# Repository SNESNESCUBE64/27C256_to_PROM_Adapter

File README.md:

# 27C256 to PROM Adapter

The purpose of this repo is to replace the old obselete PROMs. It is recommended that you use the Atmel AT27C256-45PU. It is a very fast OTP EPROM that can be purchased from reputable sellers such as mouser.com. All board designs are done in Kicad.

*Just as a disclaimer, these are not garunteed to work with everything. Not all of the adapters have been verified to work. As these are verified working, the table will be updated.*

## Chip Verification
| Chip   | Boards Made? | Verified Working? | Test Details                                                                      |
|--------|--------------|-------------------|-----------------------------------------------------------------------------------|
| 82S123 | No           | No                | Untested                                                                          |
| 82S126 | Yes          | No                | Untested                                                                          |
| 82S129 | Yes          | Yes               | Tested audio PROM 1D and Color PROM 1C on Galaga, ran for 4 hours with no issues  |
| 82S130 | Yes          | No                | Untested                                                                          |
| 82S131 | Yes          | No                | Untested                                                                          |
| 82S135 | No           | No                | Untested                                                                          |
| 82S137 | No           | No                | Untested                                                                          |
| 82S141 | No           | No                | Untested                                                                          |
| 82S141 | No           | No                | Untested                                                                          |
| 82S147 | No           | No                | Untested                                                                          |
|TKG Elim| Yes          | Yes               | Tested working on a TRS2 Radarscope PCB set. Ran with no issues.                  |

## 82S123
Just a drop in replacement, no jumpers or anything. Just solder the pins, burn the rom, then solder the rom and insert in the socket!

## 82S126/82S129/82S130/82S131
There are two jumpers, for 82S130/82S131, jump pins 1 and 2 for both jumper sets. For 82S126/82S129, jump pins 2 and 3 for both jumper sets. One thing to note with this, only the 4 low bits are used with this one. Make sure your binaries are not using the data in the upper bits.

## 82S135
Just a drop in replacement, no jumpers or anything. Just solder the pins, burn the rom, then solder the rom and insert in the socket! Uses the upper 256 bytes.

## 82S137
Just a drop in replacement, no jumpers or anything. Just solder the pins, burn the rom, then solder the rom and insert in the socket! One thing to note with this, only the 4 low bits are used with this one. Make sure your binaries are not using the data in the upper bits.

## 82S141
This one is a little bit different, it uses active circuitry to combine the chip select. It basically adds a 74ALS02 and a 0.1uF 0603 sized capacitor. The reason is because the 82S141 has four chip enables where as the 27C256 only has two. 

## TKG CPU PROM Eliminator
This is a board that combines the two PROMs found on the CPU board of Donkey Kong and Radarscope PCBs. It is more of an application than a direct PROM adapter. View the readme in the TKG CPU Eliminator folder for more details.

This has been tested and verified working on a TRS2 Radarscope PCB, but should be compatible with the following game boards:
- Radarscope (TRS2)
- Donkey Kong (TKG2)
- Donkey Kong (TKG3)
- Donkey Kong (TKG4)

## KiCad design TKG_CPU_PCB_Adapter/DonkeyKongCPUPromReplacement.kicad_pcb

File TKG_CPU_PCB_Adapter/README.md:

# TKG PROM Eliminator
This board was designed as an alternative to the bipolar PROMs commonly found on Radarscope and Donkey Kong CPU PCBs. This combines both PROMs into one single IC to save on chips in the event that the PROMs are missing or defective. Note, this is intended to be used with **AT27C256R-45PU** high speed EPROMs. These are still available as of this time, so it makes a suitable alternative. It fits into the original two sockets without any board modifications. 

## Combining the PROM Files
Because this board relies on combining both of these PROMs into one (both are 4 bit), one has to be the upper bits and the other has to be the lower bits. 2J/3E is the lower bits, 2K/3F is the upper bits. A python script has been provided to combine the files.

Use of the python script is not required. However, I wrote it so that manual shifting of the bits and merging is unecessary. The upper PROM files have to have their byte contents shifted left by 4 and then merged together. This can be done manually but is quite tedious and prone to error. The example down shows a partial merge of the first 32 bytes.

### Using the python script
The only pre-requisite is that you have to have a newer version of Python 3 installed on your computer. In order to use the python script, you will have to define the file names that you want to use in the header of the python script. You will also have to copy your PROM files into the "Scripts" folder in order to merge them.

```python
#user defined file names
promLowFilename = "TRS2_2J"
promHighFilename = "TRS2_2K"
promMergedFilename = "TRS2_MERGED"
```

promLowFilename is the file name of the 2J or 3E PROM, this is the lower bits. promHighFilename is the file name of the 2K/3F PROM, this is the upper bits. promMergedFilename is output file name.

A simple bat file is provided to easily execute it, it assumes that you have "python" as an environment variable. If you do not have that, then you will need to execute the python script another way.

### Burning the EPROM
You do not have to do anything special to burnt he eprom once you have the merged file. Duplicating to fill the EPROM is unecessary. Just load the merged PROM files at the beginning of memory for your programmer perform the programming.

## Compatibility
This has been tested and verified working on a TRS2 Radarscope PCB, but should be compatible with the following game boards:
- Radarscope (TRS2)
- Donkey Kong (TKG2)
- Donkey Kong (TKG3)
- Donkey Kong (TKG4)

It might also be compatible with Donkey Kong JR CPU PCB Boards, but I have not verified the spacing.

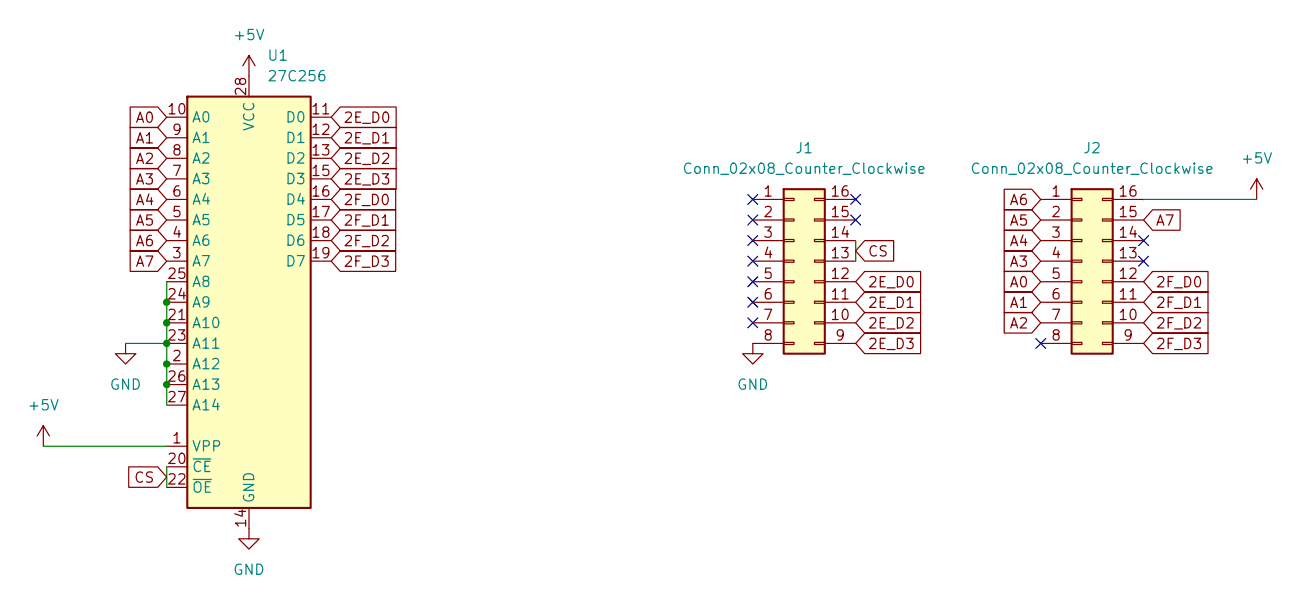
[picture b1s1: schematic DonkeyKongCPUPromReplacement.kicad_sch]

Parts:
J1, J2: Conn_02x08_Counter_Clockwise; DIP-16_W7.62mm
U1: 27C256; DIP-28_W15.24mm_Socket

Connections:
2E_D0: J1.12, U1.11 (D0)
2E_D1: J1.11, U1.12 (D1)
2E_D2: J1.10, U1.13 (D2)
2E_D3: J1.9, U1.15 (D3)
2F_D0: J2.12, U1.16 (D4)
2F_D1: J2.11, U1.17 (D5)
2F_D2: J2.10, U1.18 (D6)
2F_D3: J2.9, U1.19 (D7)
+5V: J2.16, U1.1 (VPP), U1.28 (VCC)
A0: J2.5, U1.10 (A0)
A1: J2.6, U1.9 (A1)
A2: J2.7, U1.8 (A2)
A3: J2.4, U1.7 (A3)
A4: J2.3, U1.6 (A4)
A5: J2.2, U1.5 (A5)
A6: J2.1, U1.4 (A6)
A7: J2.15, U1.3 (A7)
CS: J1.13, J1.14, U1.20 (~CE), U1.22 (~OE)
GND: J1.8, U1.2 (A12), U1.14 (GND), U1.21 (A10), U1.23 (A11), U1.24 (A9), U1.25 (A8), U1.26 (A13), U1.27 (A14)

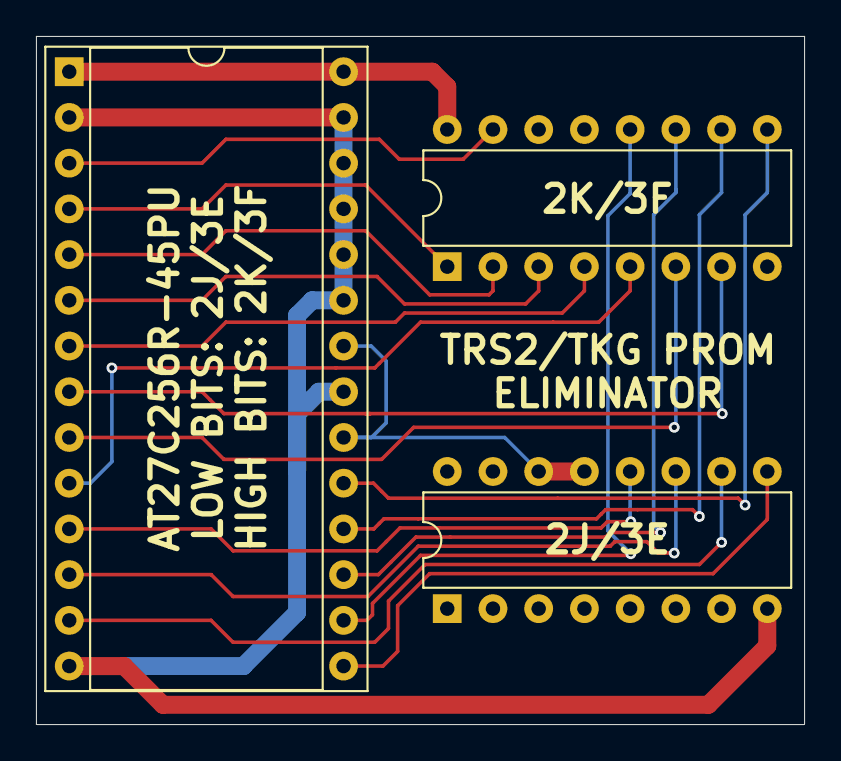
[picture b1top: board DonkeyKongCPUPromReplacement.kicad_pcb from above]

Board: 2 copper layers, 42.7 x 38.2 mm, 3 parts (0 on the bottom side), 19 nets.

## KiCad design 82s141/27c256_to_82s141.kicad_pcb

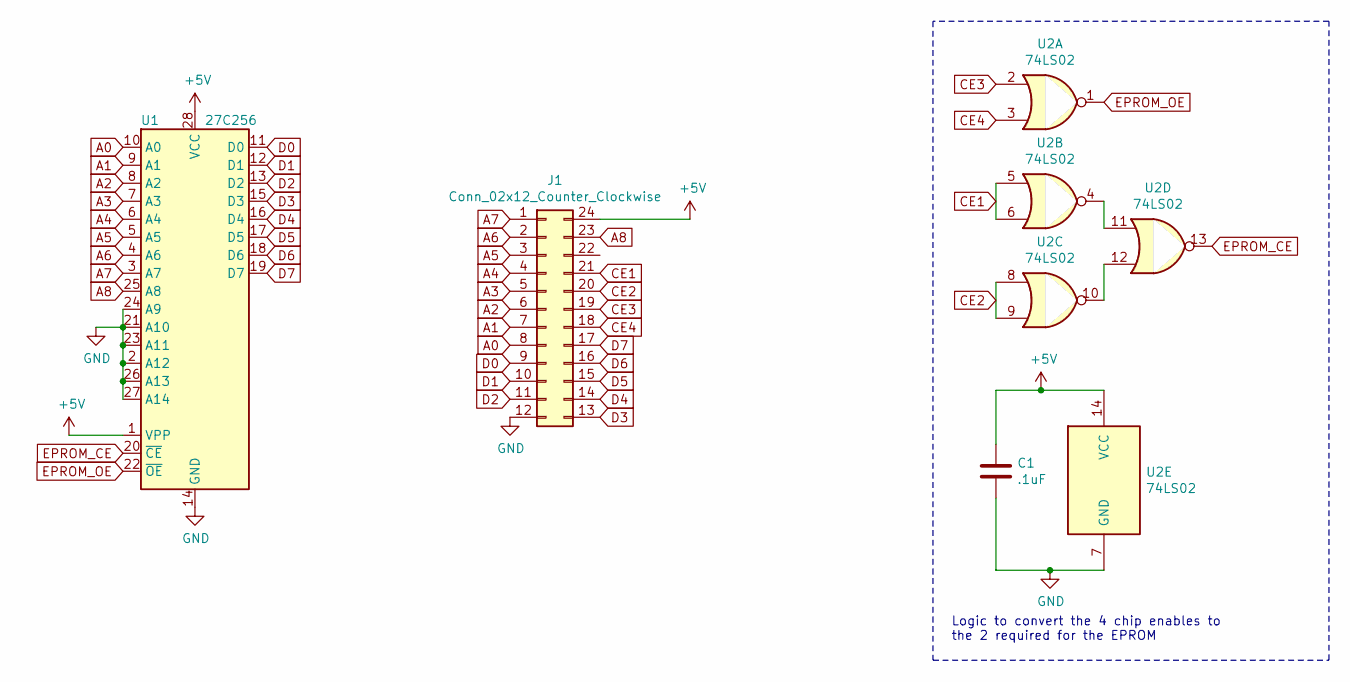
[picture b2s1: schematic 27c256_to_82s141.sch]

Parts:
C1: .1uF; C_0603
J1: Conn_02x12_Counter_Clockwise; DIP-24_W7.62mm
U1: 27C256; DIP-28_W15.24mm
U2: 74LS02; SOIC-14_3.9x8.7mm_Pitch1.27mm

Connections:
+5V: C1.1, J1.24, U1.1 (VPP), U1.28 (VCC), U2.14 (VCC)
A0: J1.8, U1.10 (A0)
A1: J1.7, U1.9 (A1)
A2: J1.6, U1.8 (A2)
A3: J1.5, U1.7 (A3)
A4: J1.4, U1.6 (A4)
A5: J1.3, U1.5 (A5)
A6: J1.2, U1.4 (A6)
A7: J1.1, U1.3 (A7)
A8: J1.23, U1.25 (A8)
CE1: J1.21, U2.5, U2.6
CE2: J1.20, U2.8, U2.9
CE3: J1.19, U2.2
CE4: J1.18, U2.3
D0: J1.9, U1.11 (D0)
D1: J1.10, U1.12 (D1)
D2: J1.11, U1.13 (D2)
D3: J1.13, U1.15 (D3)
D4: J1.14, U1.16 (D4)
D5: J1.15, U1.17 (D5)
D6: J1.16, U1.18 (D6)
D7: J1.17, U1.19 (D7)
EPROM_CE: U1.20 (~CE), U2.13
EPROM_OE: U1.22 (~OE), U2.1
GND: C1.2, J1.12, U1.2 (A12), U1.14 (GND), U1.21 (A10), U1.23 (A11), U1.24 (A9), U1.26 (A13), U1.27 (A14), U2.7 (GND)
unnamed: U2.10, U2.12
unnamed: U2.4, U2.11

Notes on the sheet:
Logic to convert the 4 chip enables to the 2 required for the EPROM

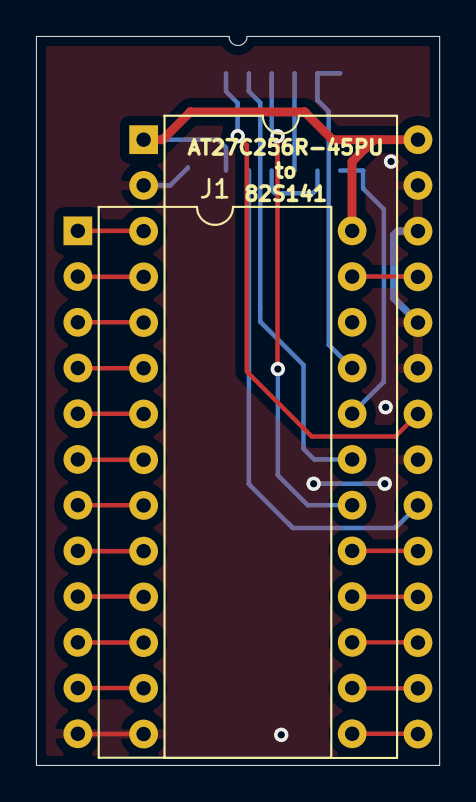
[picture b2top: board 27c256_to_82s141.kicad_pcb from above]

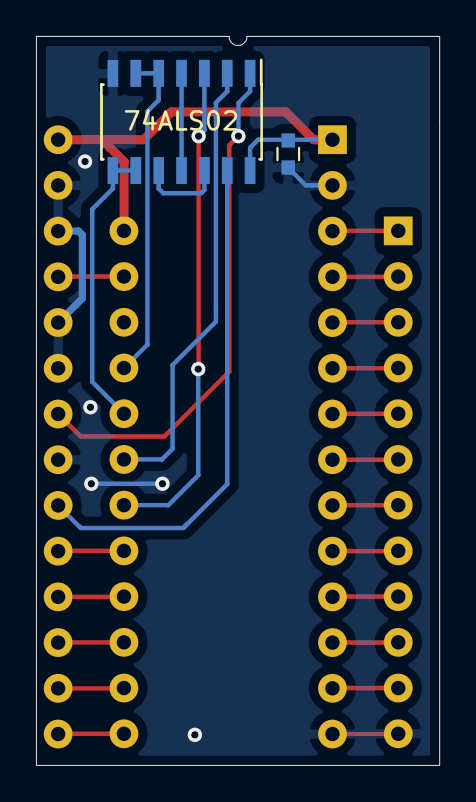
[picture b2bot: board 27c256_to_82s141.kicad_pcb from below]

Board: 2 copper layers, 22.4 x 40.5 mm, 4 parts (2 on the bottom side), 27 nets.

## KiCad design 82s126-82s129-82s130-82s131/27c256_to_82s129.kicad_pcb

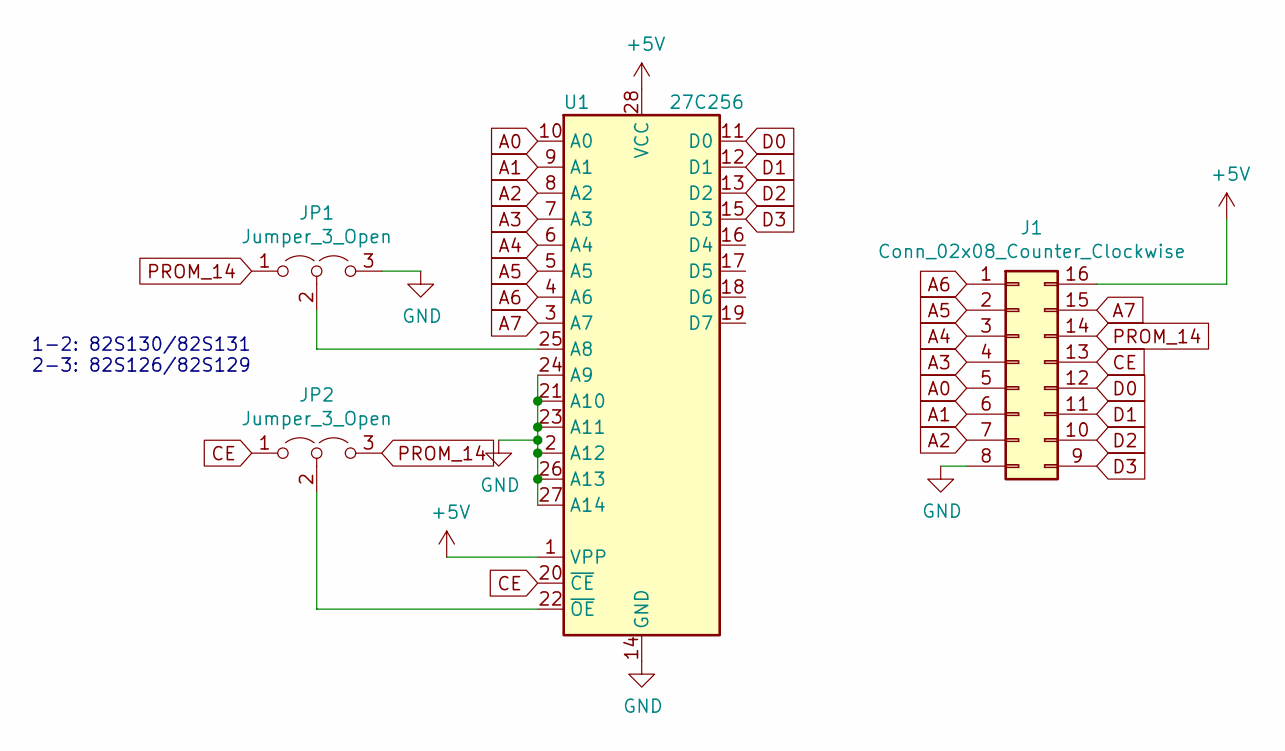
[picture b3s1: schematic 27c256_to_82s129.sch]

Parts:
J1: Conn_02x08_Counter_Clockwise; DIP-16_W7.62mm
JP1, JP2: Jumper_3_Open; GS3
U1: 27C256; DIP-28_W15.24mm

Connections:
+5V: J1.16, U1.1 (VPP), U1.28 (VCC)
A0: J1.5, U1.10 (A0)
A1: J1.6, U1.9 (A1)
A2: J1.7, U1.8 (A2)
A3: J1.4, U1.7 (A3)
A4: J1.3, U1.6 (A4)
A5: J1.2, U1.5 (A5)
A6: J1.1, U1.4 (A6)
A7: J1.15, U1.3 (A7)
CE: J1.13, JP2.1 (A), U1.20 (~CE)
D0: J1.12, U1.11 (D0)
D1: J1.11, U1.12 (D1)
D2: J1.10, U1.13 (D2)
D3: J1.9, U1.15 (D3)
GND: J1.8, JP1.3 (B), U1.2 (A12), U1.14 (GND), U1.21 (A10), U1.23 (A11), U1.24 (A9), U1.26 (A13), U1.27 (A14)
unnamed: JP1.2 (C), U1.25 (A8)
unnamed: JP2.2 (C), U1.22 (~OE)
PROM_14: J1.14, JP1.1 (A), JP2.3 (B)

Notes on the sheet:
1-2: 82S130/82S131 2-3: 82S126/82S129

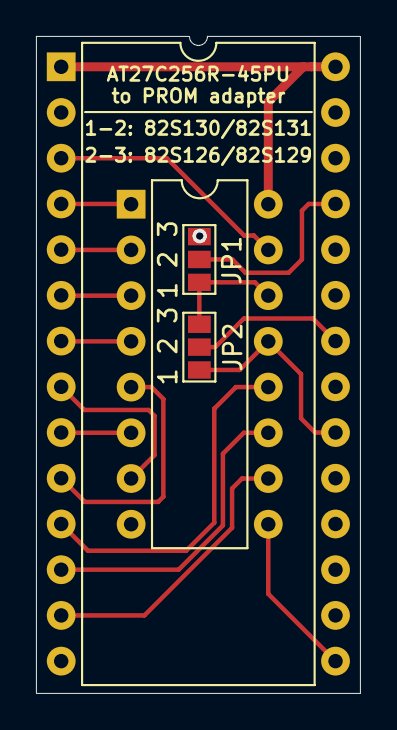
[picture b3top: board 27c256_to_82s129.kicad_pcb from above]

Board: 2 copper layers, 18.0 x 36.5 mm, 4 parts (0 on the bottom side), 18 nets.

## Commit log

2021-03-09 added 82s126 adapter
2021-03-09 added image of the first adapter
2021-03-20 Added a 82S123 adapter
2021-03-20 Changed the silkscreen on the PCB to be more specific
2021-03-20 Updated the image for the 82S123
2021-03-21 Added 82S137
2021-03-21 Added 84S141 Adapters
2021-06-23 Added 82S147 and redid 82S141
2025-12-25 Added TKG CPU PROM Eliminator
2025-12-26 Added TKG Eliminator to readme
2025-12-26 Added compatiblity section
2026-01-10 Added 82S135 Adapter
